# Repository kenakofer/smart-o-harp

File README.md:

## Summary

This site details an ongoing project to improve the chord selection mechanism on chromatic Autoharps/Chromaharps (hereafter called just "autoharps"). An arduino reads inputs from a keypad, computes the desired chord from the keypresses, and mechanically dampens the undesired strings.

It does **not** strum or pluck for the human, nor does it change chords without human input.

See [Motivations](#motivation) for why this project is useful.

See [Dampening Mechanism](#dampening-mechanism) for an for detailed analysis of dampening mechanism possibilities.

See [Avoiding harmonic nodes](#avoiding-harmonic-nodes) on the importance of considering harmonics when experimenting.

See [Keypad → Notes logic](#keypad--notes-logic) for more discussion than you wanted about sensible chord setups.

See [Wiring and Components](#wiring-and-components) to see how and with what it can be constructed.

--------

## Motivation
#### Autoharps are limited in number/variety of chords

Most autoharps have between 12 and 21 chord bars, with the ability to play in only some of the 12 musical keys. The chords available are usually major chords, minor chords, major-minor 7 chords, and sometimes a diminished chord.

Thinking just about these 4 types of chords, the maximal manual autoharp can play 21 of them, out of the `12*4=48` possible.

Stepping out of the chord bar paradigm can allow more flexibility.

#### Ergonomics of chord layouts can only go so far, and are not always key agnostic

The best layout I've found with 21 bars is to have each column be of the form (from farthest reach with the left hard to closest): `(Am, C, A7)`. Successive columns just walk this around the circle of fifths. This makes playing most major and minor songs in 5 key signatures ergonomic and *key agnostic* (transposing a song is as simple as shifting your chording hand over). Still, one of several flaws with this layout: When one wants the major/minor version of the minor/major chord, it's a wide reach that may go off the harp.

Stepping out of the 1 button = 1 chord paradigm can allow more flexibility.

#### Playing autoharps for long periods can cause cramping, arthritis, or other joint pain in the chording hand.

Depending on how well tuned the harp is and how the hand is positioned, this may be more or less of an issue. I don't play for more than an hour at a time, due to cramping.

Stepping out of the finger-force dampening paradigm etc.

----------

## Dampening mechanism

3 possibilities for this:

#### One solenoid per string

This is my current pursuit. Every string has a small solenoid positioned so that the unpowered state is dampening the string. When powered, the dampener lifts up, allowing that string to sound. The arduino controls the 30-40 solenoids individually, allowing more flexibility than the other two solutions. Cheap solenoids will cost around $1. The batteries I've tried cannot deliver the amps needed, so I'm trying a 12V, 5A laptop charger for now.

**Construction summary**: From a autoharp with exposed chord bars. Remove all bars except for one. Stretch the springs holding that bar so that the bar stays high under more force. Super glue solenoids to the sides of the bar such that the solenoids head is just short of touching the string it should dampen. Padding can then be glued to the head of the solenoid so that the resting state dampens the string effectively. Alternate placing solenoids on each side of the bar to give them enough lateral space.

**Considerations**: Size, shape, material of the dampening pads. Force of dampening. Lower notes' pads need more contact with the string to effectively dampen.

**Pros**: String by string flexibility for chord building, simple construction

**Cons**: Raised solenoids (undampened strings) draw current while remaining raised (one of my tiny $1 solenoids needs at least 70 mA to start lifting, and will continue to draw that while raised).

**Edit 01/13/2020**: On the second build iteration, I found solutions to the energy usage issues.

First, using a [voltage regulator](https://www.amazon.com/DROK-Converter-5-3V-32V-Regulator-Transformer/dp/B078Q1624B/), I was able to reduce the voltage to 9.5 or 10 volts, which reduces current through each solenoid. Each solenoid now needs about 140mA to raise.

Second, one of the solenoids only needs a tiny fraction of that power to stay raised, so the arduino can regulate down the power after a short time, greatly reducing energy costs.

This was a big problem to solve: It makes the prospect of raising all solenoids at once manageable, battery solutions are far more feasible, and the solenoids and components don't get super hot anymore!

#### Depress single-note bars with motor push

This is the second simplest solution. There are 12 "chord" bars, but their felts are cut so that one dampens only the `C`s, one dampens only the `C#`s, etc. Now to form an arbitrary chord, press down the set of bars that correspond to the pitch classes you **don't** want in the chord. Each depression will probably require more force than small solenoids can probably supply, so higher torque stepper motors may be better.

**Construction summary**: From an autoharp with exposed chord bars, take 12 bars and cut their felts to only dampen one pitch class. Replace them in a way to avoid damping on harmonic nodes. Get 12 high torque stepper motors with arms that swivel to straight down (to depress a bar). Mount them above the bars somehow, taking into account their difficult dimensions and the point of downward force on the bar relative to the strings being dampened. Given my lack of construction experience, this last task was too daunting for me.

**Considerations**: Force of dampening. Avoiding harmonic nodes.

**Pros**: Minimal power usage when not changing chords. May be cheaper than the solenoids if done effectively.

**Cons**: Complicated mounting that occupies space in front of chord bars, which may get in the way of the strumming hand.

#### Depress single-note bars with down pulling strings

I only mention this because I seriously tried making it work for a bit. Wouldn't recommend it.

Like the above in terms of the single note bars. For each bar: Tie a string to each end, run it straight downward and around a pivot point, then pull on both ends to depress the bar. Use a motor head to pull the strings taut to dampen a note.

**Considerations**: Allowing the motors to do no work when not changing chords. Motors need to have some torque.

**Pros**: The complicated mounting of the previous can be relocated somewhere less invasive (inside the autoharp body would be really interesting.

**Cons**: Starting to get quite complicated.

--------

## Avoiding harmonic nodes

See the [Wikipedia article](https://en.wikipedia.org/wiki/Harmonic) if you don't know what a harmonic node is. To experience it, place your finger or an eraser exactly halfway along a string, and pluck the string. An octave above the string's note will resonate. Slide along the string to find other points where the string will still sound.

That point on the string is a harmonic node, and is a poor location for a felt to dampen sound. There are other harmonic nodes at `(1/3, 2/3, 1/4, 3/4, 1/5, 2/5, ...)` etc. (all the rational numbers between 0 and 1). As the denominator gets bigger, it matters less in this context.

Whenever we mess with positions of bars and felts on the autoharp, we need to keep this consideration a priority to minimize extraneous noise while strumming. Consider marking all the harmonic nodes on the strings (e.g. with a red marker) before deciding on bar/felt placements that avoid those spots.

-------------

## Keypad &rarr; Notes logic

***Edit 01/13/2020***: If you don't care about motivations and thought processes, skip all this (very interesting) stuff past self wrote. I'll cover my current favorite keypad layout in [On Second Construction](#on-second-construction). That said, I still basically agree with all of this, past self just overlooked a few possibilities and didn't have enough buttons to press.

This project has the opportunity for a very consistent, learnable, ergonomic, key agnostic chord control mechanism. Optimizing for all these is a real puzzle, and different musicians will have different opinions and desires in this area.

Thankfully, the code on the arduino is far more easily changed than the mechanics of the construction, so we don't have to build a new autoharp if we forget a chord.

In this section, there will be tension between 1) incorporating more buttons/controls/physical complexity into the design, so that the amount of interaction needed to change to arbitrary chords is minimized, and 2) having fewer buttons/controls, so that the size/cost/physical complexity is minimized, but more interaction is needed to specify arbitrary chords. Each person probably has their own balance, but I lean more toward the fewer buttons/controls because I'm bad at electronics.

#### Music Theory Considerations for important triads

In a major key, here are the roman numeral chords I want easy access to, in decreasing order of importance: `(I, V(7), IV, vi, ii, II(7), iii, III(7), vii°, VI, VIIb, ...)`  I have high uncertainty after halfway through that list.

Similarly, in a minor key (using the roman numeral `vi` as the tonic chord for consistency): `(vi, iii, III(7), ii, V(7), I, IV, ...)` I have high enough uncertainty that I won't try to add more.

Songs with the richest harmonies have both minor and major progressions in them, so it behooves us to not only make the system key agnostic, but also *tonality agnostic* (a term I just made up: a song that starts major and then goes minor or vice versa shouldn't throw us for a loop).

The first 7 elements of each list have 6 in common, which (probably due to some arcane property of (meta-)music-theory) are also six-in-a-row around the circle of fifths: `(IV, I, V, ii, vi, iii)`.

Or, arranging them in rows as autoharpists typically do:

|     |     |     |
| --- | --- | --- |
| IV  | I   | V   |
| ii  | vi  | iii |

This seems like an optimal arrangement of 6 buttons for playing diatonically, to be key and tonality agnostic. I'll treat these 6 chords as the core chords, which should be accessible through a single button press.

To actually make it key agnostic though, there needs to be a way to play in more than one key.

**Fixed chord root buttons**: We could do this with static buttons by having 24 buttons that we could arrange in 2 literal circles of fifths. The circles could be one inside the other, and then we literally have a circle of fifths as a control board:

24 buttons feels like a lot, but it gives us every major/minor triad, and it could make for a really attractive circular keypad, which could rotate to "switch" keys, and have modifier keys inside or outside the main circle. You would have to construct this yourself, as I can't find such a circular keypad online, even just for one row.

If your thumb is used to joysticks, another idea is to map the sectors of a joystick's movement to the circle of fifths. The lack of tactile feedback on the boundaries between chords, or the small 30&deg; sectors might be issues.

**Dynamic chord root buttons**: We can try to use program state to do it with fewer buttons: 6 buttons could code for `(IV, I, V, ii, vi, iii)` as in the table above, and 2 buttons could be used to change our key. Each button can change the key one direction or another around the circle of fifths. This has the disadvantage of not being able to jump to some arbitrary chord root outside the key: `VIIb` and `VIb` come to mind as somewhat common examples. And the chord `vii°` is entirely in the key and we can't reach it either.

The biggest problem is that the II and III chords aren't there. Adding another row can fix that, and also gives us all of the first 7 most important chords in major and minor from above:

|     |     |     |
| --- | --- | --- |
| IV  | I   | V   |
| ii  | vi  | iii |
| II  | VI  | III |

This third row looks a little redundant next to the second row; especially if the "Swapping major/minor triad" modifier below is convenient to use.

#### Music Theory considerations for chord modifiers

We can expand the possibilities of these chords with modifiers. A modifier is a way to add or modify the notes in the 24 basic triads. Ideally, several modifiers could be added to one triad without much hassle. Each player will probably have a different preference for how these are arranged and which are included, or may even desire to change layouts between songs.

Here's my list of modifiers in decreasing order of importance and increasing order of my excitement: Adding a minor seventh, switching major/minor to minor/major triad respectively, diminishing the chord, sus4-ing the chord (!!), adding a major seventh to the chord (!!!), augmenting the chord (!!!!). There could be add2, add6, 9, 11, 13 stuff as well.

**Adding sevenths**: The major point of contention with having a `+7` modifier button is whether that 7 should be major or minor or context dependent. Chords with a major 7th above the root are rare, and seldom used outside of jazz. [Mechanical autoharps aren't great for jazz](http://jazzmando.com/new/archives/001511.shtml) (Only view if you aren't easily offended), and the possibility for major sevenths would help.

It isn't usually possible to predict the presence of major sevenths from the key signature, and chord sheets are explicit about when the 7 is major: `FM7` or `Fmaj7`. For this reason, it seems most best to use two separate modifiers: A `+min7` button that is in very easy reach for frequent use, and a `+maj7` button if the player wants it.

Alternatively, consider that a single button could be double tapped to get a different behavior, e.g. `+7` once for `+min7` and twice for `+maj7`.

**Swapping major/minor triads**: A `ii` becomes a `II`. A `iii` becomes a `III`. A common progression at the end of songs: `(I - iv - I)`. The `IV` and `V` in a major key get swapped out with their parallel minor counterparts for a more edgy harmony. The [Picardy third](https://en.wikipedia.org/wiki/Picardy_third) makes the last chord of a minor song (un)expectedly major.

Though a minor button and a major button separately are simpler to understand, the minor button would only be useful on major chords, and the major button only on minor chords. Combining them into a single button saves a button for something else.

**Diminished chords**: Three chords of interest: a [diminished triad](https://en.wikipedia.org/wiki/Diminished_triad) (3 notes with minor thirds between them), [fully diminished seventh chord] (https://en.wikipedia.org/wiki/Diminished_seventh_chord) (4 notes with minor thirds between them), and [half-diminished seventh chord](https://en.wikipedia.org/wiki/Half-diminished_seventh_chord) (a diminished triad with a minor seventh on top). The logic I've used thus far does not fit diminished chords well: We don't have `vii°` the most common diminished triad in our base triads; if we did, we still don't have a modifier to add a minor sixth to the chord for the fully diminished seventh. The most comprehensible solution is simply to add a modifier for each variation.

There are a few inelegant hacks we can use if we don't want to add so many buttons for these relatively rare chords. We could add one modifier button, a `dim` button, but have the button work in coordination with our `V` triad to produce the `vii°`. Why `V`? The diminished triad has a (dominant function)[https://en.wikipedia.org/wiki/Dominant_(music)] just like the `V`, and a `V7` can be thought of as a `vii°` with an added fifth scale degree.

We can co-opt other buttons that will not be much use in diminished chords, such as the `+maj7`, to be a `+min6` for the fully diminished chord. We can use the `+min7` as is to produce a half-diminished chord. Each of these chords would require 3 button presses: the `V`, the `dim`, and whichever `+7` button.

**Augmented chords**: These are a piece of proverbial cake relative to the diminished chords. An [augmented triad](https://en.wikipedia.org/wiki/Augmented_triad) is 3 notes separated by major thirds. Ignoring enharmonics (as I do) there are only 3 different augmented chords. So throw on an `aug` button, hit it with `I` or `iii` and you'll get the same effect. The `+7` modifiers are still there if you want to play a really exotic chord.

**Sus4 chords**: In a [sus4 chord](https://en.wikipedia.org/wiki/Suspended_chord) the 3rd is removed and a perfect 4th added. Pretty straightforward unless you want to hack together a more general system to get `sus2` without extra buttons, but I'm cool with just a `sus4` for now.

**You get the idea**: Other modifier ideas: removing the third to make open fifths, removing third and fifth to make octaves (yawn). "Scale" modifiers could be used for allowing playing any notes inside the scale by damping the ones outside the scale. Diatonic scale, pentatonic scale, various minor scales, or other less common scales.

#### Misc. operator buttons

**Left/Right around the circle of fifths**: 2 buttons, `mod5` and `mod4` to allow the instrument to change keys in two directions: `V` becomes `I`; and `IV` becomes `I`. Modulating by minor thirds might also be useful to go quickly between parallel major/minor keys.

**Previous chord**: There are frequently times when you are walking a melody up a scale and have to go back and forth between passing chords. Having a `prev` button to go to the chord just before the one currently playing could save 1 or 2 key presses depending on how complicated the chords are.

#### Keypress timing considerations

Timing is very important and has not yet been discussed. Some keypads do not support detecting multiple keys pressed at the same time, so combinations of keys pressed to produce a chord cannot happen at once. We will call this a _sequential_ keypad system. Many more keypads have, at least in their hardware, the ability to correctly detect certain simultaneous keypresses, but not others. We'll call a system that can detect some number of simultaneous keypresses correctly a _simultaneous_ keypad system. We'll start with thinking sequentially for simplicity's sake.

#### Sequential principles

Most of the time when you press the `IV` button, you just want to play that chord as is. But suppose one time in the middle of a song it's a minor `iv` chord, requiring the major/minor modifier plus the `IV` button. Thinking sequentially, one button press has to come before the other.

If the `IV` is first, the arduino can either 1) wait for more input, or 2) immediately make the chord available with possibly the wrong tonality.

If the `maj/min` is first, the arduino can either 3) wait for more input, or 4) immediately change the current chord to the opposite tonality.

Of these 4 scenarios, I like 3 best. Immediate changes mean the instrument will be in states of the wrong tonality. If the arduino is to wait for something, it's best that the "something" be definite. We've talked about the 6 fundamental triad controls, and one reason they are so fundamental is that they are the common element, and thus can safely be the element that actuates the changing of the chords in one quick motion.

Say we're in C major, and we want to play `E7`, which is `III7`. So the order of the sequential presses would be `maj/min`, `+m7`, `iii`. Only pressing the final button would cause the dampened strings to change. Not gonna lie: this sounds painful given how often I use `III7`.

#### Sequential layout ideas

Given the above, here are some of my ideas for "good" sequential keypad layouts. Any of these could have part or all of it rotated 90&deg; to better fit under the fingers.

**12 button sequential keypad A (fast and simple):**

|     |     |     |
| --- | --- | --- |
| IV  | I   | V   |
| ii  | vi  | iii |
| II7 | VI7 | III7|
| mod4|+min7| mod5|

This layout should play melodies quickly and efficiently. The presence of the third triad row (with 7s already added because of their nearly universal use on secondary dominants) allows us to leave out `maj/min` modifier. We can play most chords with a single keypress, with the exception of the `V7` (this is a real downer). Even with just these 12 buttons, the player can play in all 12 key signatures, major and minor, with the most common chords, have minor chords with minor sevenths, major sevenths if you use a double-tap logic, and modulate keys mid song without fuss. 

Some players might like swapping out the `+min7` for a `V7` button, or have the double tap behavior provide the `V7`, or some variation on that.

**12 button sequential keypad B (slower and deeper):**

|     |     |     |
| --- | --- | --- |
| IV  | I   | V   |
| ii  | vi  | iii |
|+min7|maj/min|sus4|
| mod4|prev | mod5|

We remove our convenience row of chords to add more cool modifiers to show off with. Double taps would open open up more possibilities `+min7`  &rarr; `+maj7`; `maj/min` &rarr; `dim`; `sus4`  &rarr; `sus2`. But here the secondary dominants with sevenths require 3 presses. This could be fine for chording and slower melodies, but not faster ones. The `prev` button recovers some speed between alternating chords.

#### Simultaneous principles in row, column keypads

The possibility of pressing multiple keys at the same time allows for faster fingering of chords with modifiers, but introduces complexities of hardware and timing. For a better introduction to these issues on a typical computer keyboard, [see here](https://en.wikipedia.org/wiki/Rollover_(key)).

**No ground pin**: It's common for keypads to be wired such that each row and column corresponds to a pin, such that pressing the button in the first row and first column connects the first row pin (`row1`) to the first column pin (`col1`). Suppose that the button in the first row, second column is also pressed. then `row1`, `col1`, and `col2` are all connected to each other.

But the arduino's logic is in reverse: (Ex. 1) If it sees that `row2`, `col3`, and `col4` are connected to each other, can it know for certain what buttons are pressed? In this case, yes, because a button press is always at the intersection of a row and column, and a row or column pin can't be in the connected list without having a pressed button. We can extend this logic to say that any number of keypresses in any single row or in any single column are always safely distinguishable.

(Ex. 2) If `row1` and `col1` are connected, and `row2` and `col2` are separately connected, the arduino still knows the exact two buttons that are pressed. This, along with the first example, shows that any two simultaneous keypresses are distinguishable.

Certain combinations of 3 simultaneous keypresses introduce ambiguity. (Ex. 3) If ever there is a pressed button (e.g. `row1, col1`) who has another pressed button buddy in their row (`row1, col2`), and also a pressed button buddy in their column (`row2, col1`), then all the arduino sees is a group of 4 connected pins: `row1`, `row2`, `col1`, `col2`. Some combination of 3 or 4 of these were pressed, but there's no way to know which. 

However, ambiguity is not necessarily a deal-breaker: as long as the arduino has a sensible default for how to interpret specific situations of ambiguity, it can use that default. We just want to avoid designing a system that allows two useful "button signatures" to have the same "pin signature" from the arduino's perspective.

**With ground pin**: My keypad is weird in that it has a pin that connects to every button, which I'll call the `ground`. So pressing the top left button connects `row1`, `col1`, and `ground`. So Ex. 2 isn't a possibility, because all button presses connect the entire set of row and column pins involved. So the only unambiguous button presses are, as descibed in Ex. 1, within a single column or within a single row. The same note about ambiguity applies.

I'm honestly not sure where I got this keypad, or why I would want this `ground` pin when it seems to only decrease the functionality.

**Regardless**, it is safe for us to make plans for simultaneous keypresses in a single row or column. This limitation still allows quite a few possibilities, but makes simultaneous modifier keys, like a `+min7` difficult to put somewhere that is usable by all the relevant chords. As a result, I'll try to avoid having modifier keys at all.

**12 button simultaneous keypad (Bear With Me edition):**

This will get kind of complicated to diagram now. It's better to have lots of choices IMHO, but I realize many will disagree with me. Note that "2 buttons to the left" will sometimes mean wrapping back around to the right side.

**Interpretation:** Default chord (chord when button to the left is also pressed) (chord when the 2 buttons to the left are both pressed)

|     |     |     |     |
| --- | --- | --- | --- |
|  VIIb (vii°) (vii°7) | IV (IV7) (IVmaj7) | I (I7) (Imaj7)  | V (V7) (Vmaj7)   |
| v (iv) (i)  | ii (II7) (ii7) | vi (VI7) (vi7) | iii (III7) (iii7) |
| mod4 | prev | +sus4 | mod5 |

First off, I sincerely apologize for the first column, you may ignore it as you are picking up the pattern of the rest of the table. 

Pressing a bunch of buttons in a row are interpreted as a modifier on the rightmost of the buttons pressed (wrapping from left to right is important, e.g. to get the `vii°` one would press `VIIb` and `V`). This mostly serves to add various sevenths to chords, and differs between the major and minor triads.

**Major**: When 1 button to the left is pressed, it does `+min7`. When 2 buttons are pressed, it `+maj7`s the chord.

**Minor**: When 1 button to the left is pressed, it majors it and does `+min7`. When 2 buttons are pressed, it just `+min7`s the chord. I didn't use `+maj7` because that isn't as much used on minor chords.

And the first column just throws in all the things I would be sad not to have, in a vaguely circle-of-fifths-y way. This layout throws easy comprehension out the window in favor of packing in the options in an ergonomic manner (Imagine alternating between fingerings for `I` and `V7`, just by lifting a single finger, or doing the same between `III7` and `vi`).

Note that on a grounded pin keypad, the `+sus4` introduces ambiguity when pressed simultaneously with, say, `V`. It connects pins `row3`, `col3`, `row1`, and `col4`. However, if we are content with only using `+sus4` with a single other button press, and not using the other buttons in the 3rd row with the triad buttons, we can have the arduino interpret this ambiguity predictably as using the `+sus4` with whichever button is diagonal to it. No-ground-pin keypads don't need to worry about this.

I'm not sure how useful the `prev` button will be in this layout, because most back-and-forth passing chords are pretty easy to go between already. I add it here mostly because I don't know what else to put in that space. I can't have another typical modifier due to the paragraph above. I could have a parallel minor modifier that is only used with the `mod4` and `mod5` buttons to change key up or down by a minor 3rd easily. Or I could put another chord there, like the `VIb`.

## On Second Construction

This section is written much later. On the second construction attempt, I solved a lot of major issues.

I started over building because the first build was cludgy and bad in its
unfinished state. Here are the major changes in the second construction, in
the software:

 - Using 16 button keypad (4 column, 4 row pins, no weird ground pin
 this time ;) This allows:
 - Different button reading strategy: Use two dimensional array of
 button states rather than row and column states. This allows a lot more
 keypresses without ambiguity.
 - Keymapping to chords substantially rethought. Now it doesn't use ANY
 simultaneous keypresses, but considers some keys as "modifiers" which
 don't do anything when pressed on their own, and "actuators" (maybe
 find better name?) which when pressed immediately actuate a chord with
 whatever modifiers are down. See the big comment in the code for the
 layout.
 - The above means that we were able to get rid of the `buffer_chord`
 system entirely! :celebrate:
 - Chords can now have up to 5 notes to allow for things like Dominant 9
 chords. No reason it couldn't be more.
 - Major power reduction by using pin 10 on the arduino to change
 current flowing to the solenoids. The solenoids need lots more power to
 pop up than they need to stay up, so every chord change starts at
 `FULL_POWER` then drops power usage considerably to `LOW_POWER` after
 `TICKS_AT_FULL_POWER` ticks.
 - Pasted in the function `setPwmFrequency` to use on pin 10, because
 the default, slower frequencies cause audible hums during `LOW_POWER`

Major changes in the hardware that weren't mentioned in the software:

 - I'm now soldering female header pin connectors rather than the components themselves into the soldering board. If I fry another Arduino Nano or break a keypad it will be a trivial swap-out rather than a solder-mess project-killer.
 - Similarly, on each solenoid, I'm putting a jumper cable head on one of the wires. This way, it can be plugged in rather than soldered in. Same logic as above, and flexibility of rewiring on the fly if the autoharp strings are tuned to different pitches.
 - I'm now using a [voltage regulator](https://www.amazon.com/DROK-Converter-5-3V-32V-Regulator-Transformer/dp/B078Q1624B/), which helps me fiddle with and monitor power better. It might not be necessary in the long run, but for a prototype it is _incredibly_ handy to simply bump the voltage up or down.
 - I'm not trying to incororate LEDs this time around. Simpler design, more in my pay grade.

### Most recent keypad layout (4x4 buttons)

My new keypad's hardware doesn't have ambiguity unless 3 or more button presses are at the corners of a rectangular area. This allows some clever setup of held (not simultaneous press!) modifier keys. Getting rid of simultinaety is huge I think.

**Single press with single modifier**

|     |     |     |     |
| --- | --- | --- | --- |
| VIIb | IV | I | V |
| ii | vi | iii | vii° |
| _Make Do_ | _Sus2_ | _Sus4_ | _Maj/Min_ |
| _mM7_ | _MM7_ | _mm7_ | _Mm7_ |

**Single press with double modifier in vertical stacks**

|     |     |     |     |
| --- | --- | --- | --- |
| VIIb | IV | I | V |
| ii | vi | iii | vii° |
| _Dim_ | _Aug_ | _Dim7_ | _1/2 Dim 7_ |
| _(^^^)_ | _(^^^)_ | _(^^^)_ | _(^^^)_ |

Note that:

 - The arrows _(^^^)_ mean that both modifiers must be pressed for the listed modifier to apply. Still, nothing will actuate until a chord button is pressed.
 - Because these modifiers are vertically stacked, it is impossible for a single chord button to form a rectangular area, so hardware ambiguity is avoided.

**Single press with double modifier in diagonal combinations**

|     |     |     |     |
| --- | --- | --- | --- |
| VIIb | IV | I | V |
| ii | vi | iii | vii° |
| | | _Dom9_ | |
|  |  |  | _(Dom9)_ |

Note that:

 - I'm not sure how well these combos will work ergonomically, so I'm only trying one for now. _Dom9_ means Root, M3, P5, m7, M9(M2).
 - Once again, these diagonal combinations avoid hardware ambiguity when one of the chord buttons is pressed

**Horizontal Double modifier as chord button:**

|     |     |     |     |
| --- | --- | --- | --- |
| VIIb | IV | I | V |
| ii | vi | iii | vii° |
| | | VIb | (<<<) |
|  |  | IIIb | (<<<) |

 - These horizontally aligned modifiers would NOT work unambiguously with all chord buttons (If the `I` were pressed, it would look like `V` was also pressed), so it seems reasonable to actually make the modifiers actuate in combination with each other. This means that these particular chords can't have modifiers applied to them to make, for example, a VIb seventh chord.
 - Not all slots are used, because most other chords we really want to be able to add other modifiers

 I'll update the Wiring and Components section at some point, it's outdated for now

--------

## Outdated Wiring and Components

3 main topics here, which others have covered pretty well already so I don't need to. Click the links to read more.

1. [8-bit shift registers](https://www.arduino.cc/en/tutorial/ShiftOut): Getting the (at least) 12 outputs necessary to control 12 systems of solenoids independently, without using up all the arduino's pins.

2. [Driving solenoids with an arduino](https://core-electronics.com.au/tutorials/solenoid-control-with-arduino.html): Except that we will drive the solenoids and the arduino off the same power source, so maybe this isn't super relevant.

3. [Keypad input method](https://www.instructables.com/id/Arduino-Button-Tutorial/): having the arduino read in button presses. This is basic input/output stuff, and the linked tutorial is excellent for looking at a single case. I've covered the specific convoluted logic of my keypad already.

Here's my breadboard setup all laid out. This is diagram version 2, using the nano and fixing some wire placement issues from the first version. 

**Disclaimer**: I'm not great at electronics as I write this. I fried several components on my way to what I hope is a safe, working design.

#### Diagram notes

For every one solenoid shown in the diagram, there will be upwards of 4 solenoids wired in parallel with it, so that all the `C` solenoids share a transistor, and so do the `C#` solenoids etc.

The 4 "extra" outputs could be used to wire the 4 bottom strings of the autoharp individually, so that you can have, for example, the `G7` chord not include the bottom `F`, but still include all the other `F`s.

Other than using 12V to power the arduino on the Vin pin, keep the 12V as far away from the arduino as possible. I fried one Nano by momentarily bridging a connection from 12V to the Nano's 5V pin.

#### Outdated Components list

 * I used [this SB1660 busboard](https://www.amazon.com/gp/product/B00LLOOA0U) for soldering a semi-permanent prototype.
 * Arduino Nano
 * 12V, 5A power supply
 * 2 x 74HC595 chip
 * 12-16 x 1kΩ resistors
 * ~36 x [12V 120mA spring push pull solenoids](https://www.ebay.com/itm/12V-DC-Suction-Micro-Electromagnet-Spring-Push-Pull-Type-Rod-Solenoid-Magnet-4mm/153089629798) (You need one for each autoharp string.)
 * 12-16 x 2N2222 (NPN, BJT) transistors
 * 12-16 x 1N4001 diodes

----

## Code

[Here's the code](https://github.com/kenanbit/smart-o-harp/blob/master/code/code.ino). It's fairly straightforward.

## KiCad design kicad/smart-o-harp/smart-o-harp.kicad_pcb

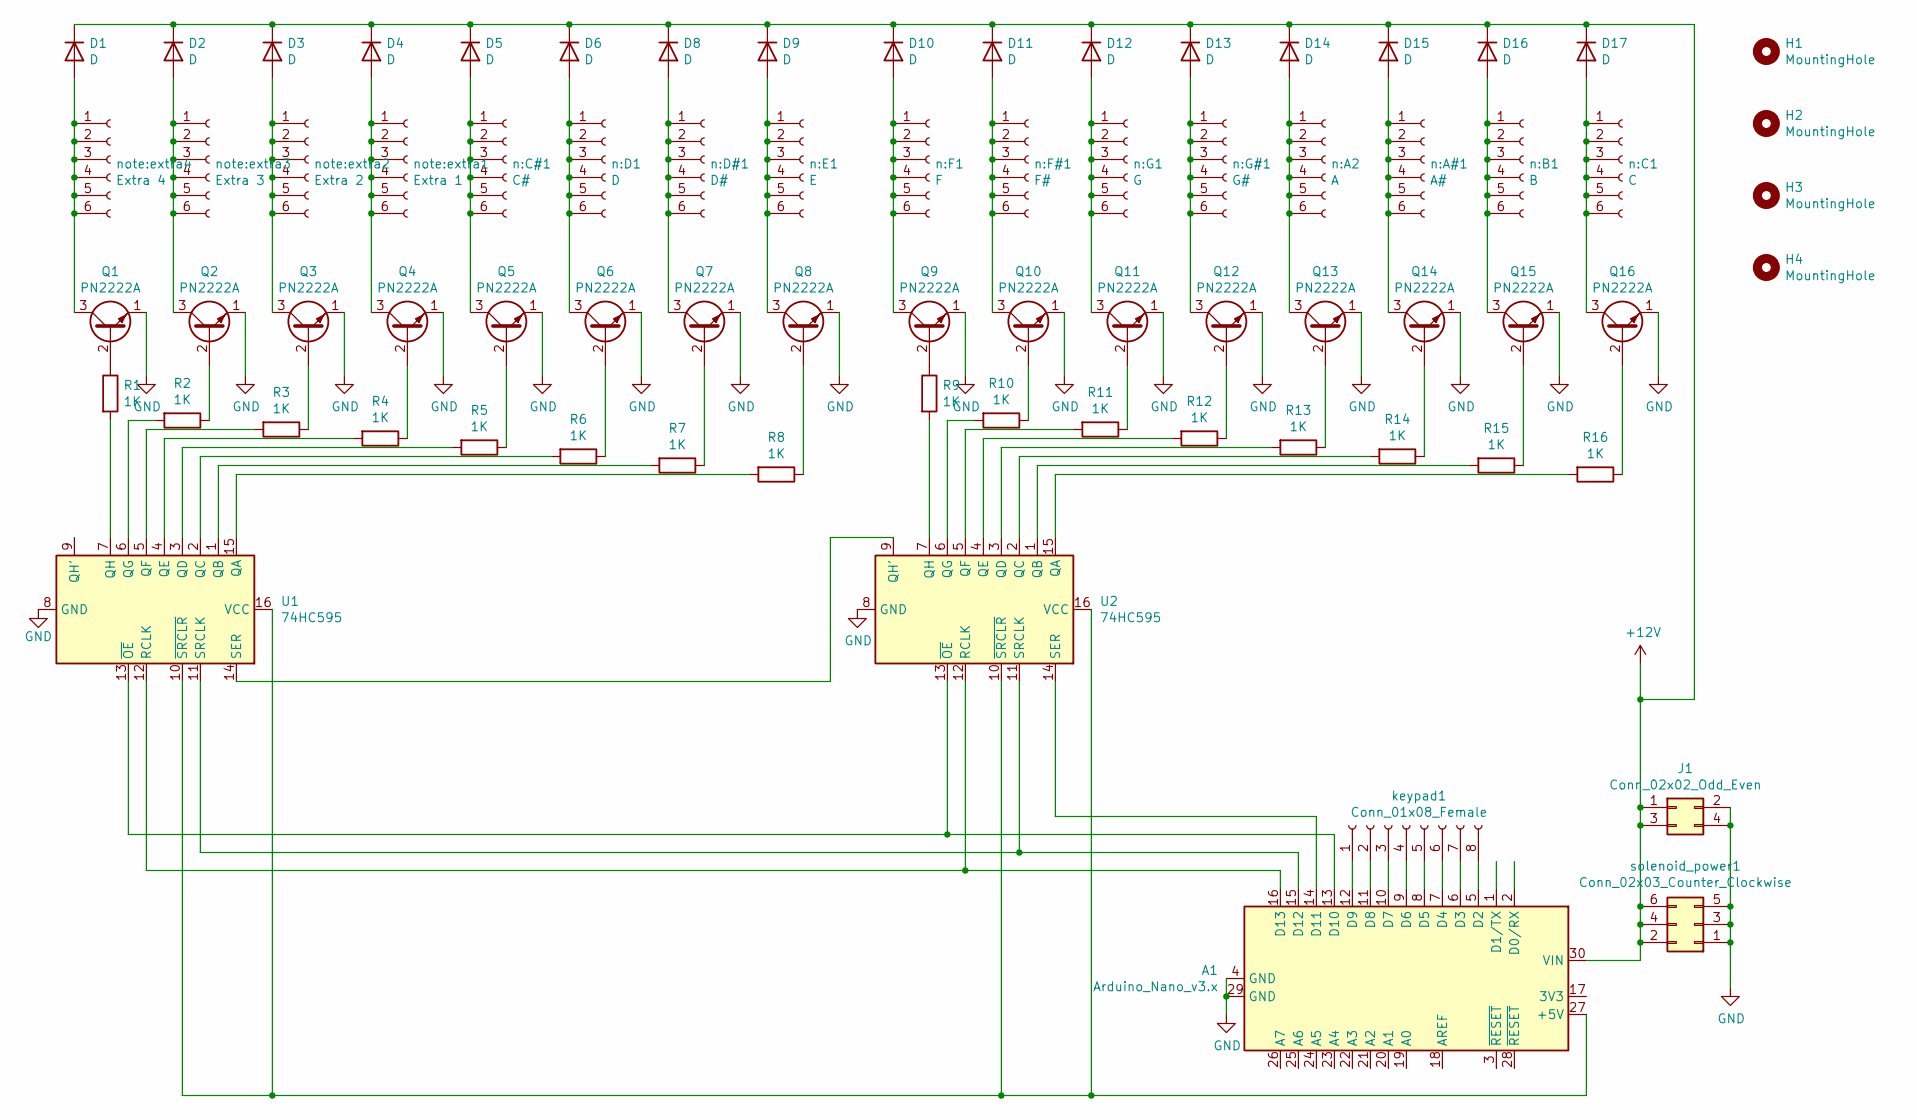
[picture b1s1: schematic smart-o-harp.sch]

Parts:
A1: Arduino_Nano_v3.x; Arduino_Nano
D1, D2, D3, D4, D5, D6, D8, D9, D10, D11, D12, D13, D14, D15, D16, D17: D; D_A-405_P5.08mm_Vertical_AnodeUp
H1, H2, H3, H4: MountingHole; MountingHole_3.2mm_M3
J1: Conn_02x02_Odd_Even; PinHeader_2x02_P2.54mm_Vertical
Q1, Q2, Q3, Q4, Q5, Q6, Q7, Q8, Q9, Q10, Q11, Q12, Q13, Q14, Q15, Q16: PN2222A; TO-92_Wide
R1, R2, R3, R4, R5, R6, R7, R8, R9, R10, R11, R12, R13, R14, R15, R16: 1K; R_Axial_DIN0204_L3.6mm_D1.6mm_P5.08mm_Horizontal
U1, U2: 74HC595; DIP-16_W7.62mm
keypad1: Conn_01x08_Female; PinHeader_1x08_P2.54mm_Vertical
n:A2: A; PinHeader_1x06_P2.54mm_Vertical
n:A#1: A#; PinHeader_1x06_P2.54mm_Vertical
n:B1: B; PinHeader_1x06_P2.54mm_Vertical
n:C1: C; PinHeader_1x06_P2.54mm_Vertical
n:C#1: C#; PinHeader_1x06_P2.54mm_Vertical
n:D1: D; PinHeader_1x06_P2.54mm_Vertical
n:D#1: D#; PinHeader_1x06_P2.54mm_Vertical
n:E1: E; PinHeader_1x06_P2.54mm_Vertical
n:F1: F; PinHeader_1x06_P2.54mm_Vertical
n:F#1: F#; PinHeader_1x06_P2.54mm_Vertical
n:G1: G; PinHeader_1x06_P2.54mm_Vertical
n:G#1: G#; PinHeader_1x06_P2.54mm_Vertical
note:extra1: Extra 1; PinHeader_1x06_P2.54mm_Vertical
note:extra2: Extra 2; PinHeader_1x06_P2.54mm_Vertical
note:extra3: Extra 3; PinHeader_1x06_P2.54mm_Vertical
note:extra4: Extra 4; PinHeader_1x06_P2.54mm_Vertical
solenoid_power1: Conn_02x03_Counter_Clockwise; PinHeader_2x03_P2.54mm_Vertical

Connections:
+12V: A1.30 (VIN), D1.1 (K), D2.1 (K), D3.1 (K), D4.1 (K), D5.1 (K), D6.1 (K), D8.1 (K), D9.1 (K), D10.1 (K), D11.1 (K), D12.1 (K), D13.1 (K), D14.1 (K), D15.1 (K), D16.1 (K), D17.1 (K), J1.1, J1.3, solenoid_power1.2, solenoid_power1.4, solenoid_power1.6
GND: A1.4 (GND), A1.29 (GND), J1.2, J1.4, Q1.1 (E), Q2.1 (E), Q3.1 (E), Q4.1 (E), Q5.1 (E), Q6.1 (E), Q7.1 (E), Q8.1 (E), Q9.1 (E), Q10.1 (E), Q11.1 (E), Q12.1 (E), Q13.1 (E), Q14.1 (E), Q15.1 (E), Q16.1 (E), U1.8 (GND), U2.8 (GND), solenoid_power1.1, solenoid_power1.3, solenoid_power1.5
unnamed: A1.5 (D2), keypad1.8
unnamed: A1.6 (D3), keypad1.7
unnamed: A1.7 (D4), keypad1.6
unnamed: A1.8 (D5), keypad1.5
unnamed: A1.9 (D6), keypad1.4
unnamed: A1.10 (D7), keypad1.3
unnamed: A1.11 (D8), keypad1.2
unnamed: A1.12 (D9), keypad1.1
unnamed: A1.13 (D10), U1.13 (~OE), U2.13 (~OE)
unnamed: A1.14 (D11), U2.14 (SER)
unnamed: A1.15 (D12), U1.11 (SRCLK), U2.11 (SRCLK)
unnamed: A1.16 (D13), U1.12 (RCLK), U2.12 (RCLK)
unnamed: A1.27 (+5V), U1.10 (~SRCLR), U1.16 (VCC), U2.10 (~SRCLR), U2.16 (VCC)
unnamed: D1.2 (A), Q1.3 (C), note:extra4.1, note:extra4.2, note:extra4.3, note:extra4.4, note:extra4.5, note:extra4.6
unnamed: D2.2 (A), Q2.3 (C), note:extra3.1, note:extra3.2, note:extra3.3, note:extra3.4, note:extra3.5, note:extra3.6
unnamed: D3.2 (A), Q3.3 (C), note:extra2.1, note:extra2.2, note:extra2.3, note:extra2.4, note:extra2.5, note:extra2.6
unnamed: D4.2 (A), Q4.3 (C), note:extra1.1, note:extra1.2, note:extra1.3, note:extra1.4, note:extra1.5, note:extra1.6
unnamed: D5.2 (A), Q5.3 (C), n:C#1.1, n:C#1.2, n:C#1.3, n:C#1.4, n:C#1.5, n:C#1.6
unnamed: D6.2 (A), Q6.3 (C), n:D1.1, n:D1.2, n:D1.3, n:D1.4, n:D1.5, n:D1.6
unnamed: D8.2 (A), Q7.3 (C), n:D#1.1, n:D#1.2, n:D#1.3, n:D#1.4, n:D#1.5, n:D#1.6
unnamed: D9.2 (A), Q8.3 (C), n:E1.1, n:E1.2, n:E1.3, n:E1.4, n:E1.5, n:E1.6
unnamed: D10.2 (A), Q9.3 (C), n:F1.1, n:F1.2, n:F1.3, n:F1.4, n:F1.5, n:F1.6
unnamed: D11.2 (A), Q10.3 (C), n:F#1.1, n:F#1.2, n:F#1.3, n:F#1.4, n:F#1.5, n:F#1.6
unnamed: D12.2 (A), Q11.3 (C), n:G1.1, n:G1.2, n:G1.3, n:G1.4, n:G1.5, n:G1.6
unnamed: D13.2 (A), Q12.3 (C), n:G#1.1, n:G#1.2, n:G#1.3, n:G#1.4, n:G#1.5, n:G#1.6
unnamed: D14.2 (A), Q13.3 (C), n:A2.1, n:A2.2, n:A2.3, n:A2.4, n:A2.5, n:A2.6
unnamed: D15.2 (A), Q14.3 (C), n:A#1.1, n:A#1.2, n:A#1.3, n:A#1.4, n:A#1.5, n:A#1.6
unnamed: D16.2 (A), Q15.3 (C), n:B1.1, n:B1.2, n:B1.3, n:B1.4, n:B1.5, n:B1.6
unnamed: D17.2 (A), Q16.3 (C), n:C1.1, n:C1.2, n:C1.3, n:C1.4, n:C1.5, n:C1.6
unnamed: Q1.2 (B), R1.1
unnamed: Q2.2 (B), R2.1
unnamed: Q3.2 (B), R3.1
unnamed: Q4.2 (B), R4.1
unnamed: Q5.2 (B), R5.1
unnamed: Q6.2 (B), R6.1
unnamed: Q7.2 (B), R7.1
unnamed: Q8.2 (B), R8.1
unnamed: Q9.2 (B), R9.1
unnamed: Q10.2 (B), R10.1
unnamed: Q11.2 (B), R11.1
unnamed: Q12.2 (B), R12.1
unnamed: Q13.2 (B), R13.1
unnamed: Q14.2 (B), R14.1
unnamed: Q15.2 (B), R15.1
unnamed: Q16.2 (B), R16.1
unnamed: R1.2, U1.7 (QH)
unnamed: R2.2, U1.6 (QG)
unnamed: R3.2, U1.5 (QF)
unnamed: R4.2, U1.4 (QE)
unnamed: R5.2, U1.3 (QD)
unnamed: R6.2, U1.2 (QC)
unnamed: R7.2, U1.1 (QB)
unnamed: R8.2, U1.15 (QA)
unnamed: R9.2, U2.7 (QH)
unnamed: R10.2, U2.6 (QG)
unnamed: R11.2, U2.5 (QF)
unnamed: R12.2, U2.4 (QE)
unnamed: R13.2, U2.3 (QD)
unnamed: R14.2, U2.2 (QC)
unnamed: R15.2, U2.1 (QB)
unnamed: R16.2, U2.15 (QA)
unnamed: U1.14 (SER), U2.9 (QH')

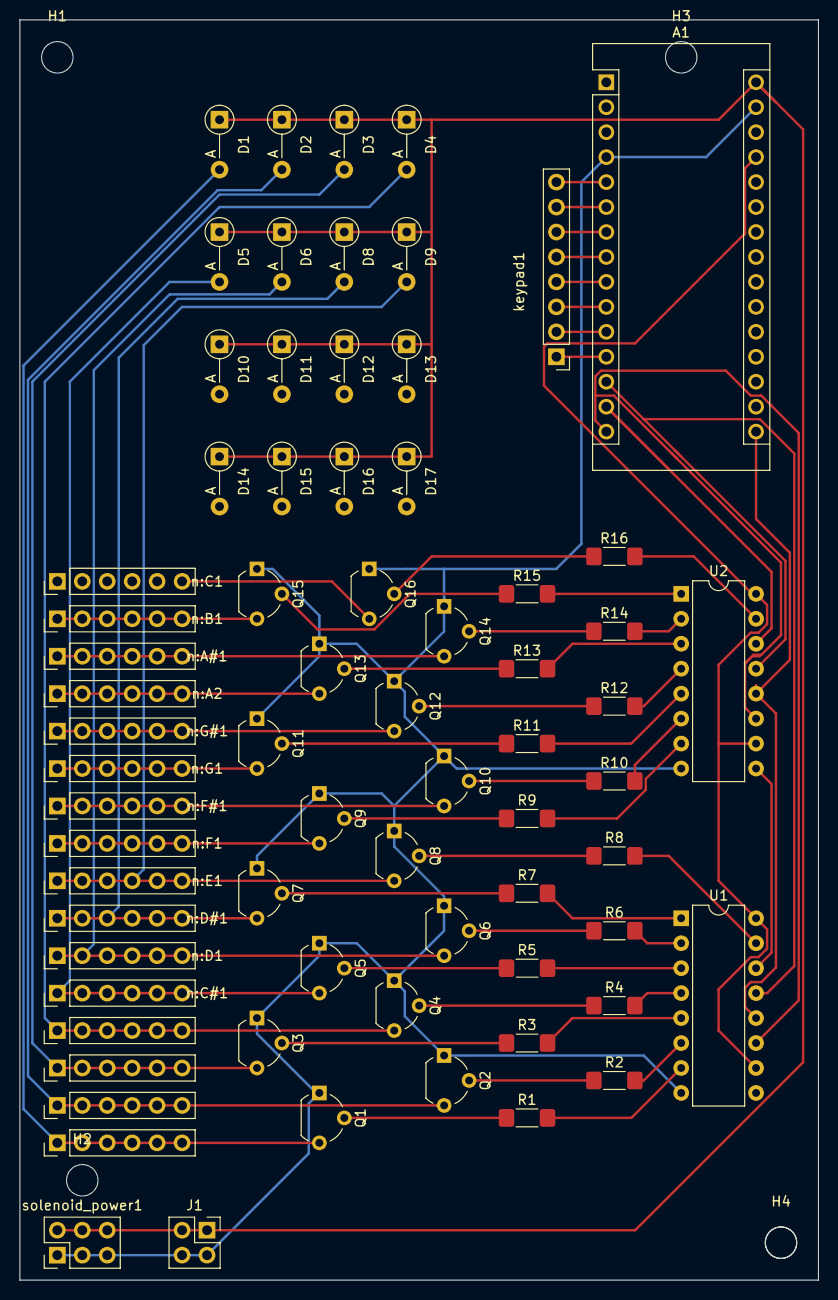
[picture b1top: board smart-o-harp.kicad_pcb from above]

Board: 2 copper layers, 81.3 x 128.3 mm, 74 parts (0 on the bottom side), 64 nets.

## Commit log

2019-03-29 Set theme jekyll-theme-time-machine
2019-03-29 Create basic description of project
2019-03-29 Remove unnecessary title in README
2019-03-29 Add <hr>s, h2s
2019-03-29 Add dampening mechanism section
2019-03-29 bold not
2019-03-29 Add avoiding harmonic nodes
2019-03-29 Add beginnings of keypad to notes logic
2019-04-01 Copy default.html from theme
2019-04-01 Remove current-section header
2019-04-01 Create style.scss for better mobile width
2019-04-01 diminished, augmented, sus4
2019-04-01 Fix lots of css
2019-04-01 Add keypress timings
2019-04-02 Add nice coloring to code blocks
2019-04-02 fix degree signs
2019-04-02 Add 12 button layouts
2019-04-02 Fix typos
2019-04-02 Add icons
2019-04-02 Add links to favicon
2019-04-03 Add simultaneous principles/example
2019-04-03 Remove padding on table cells, min-height/width
2019-04-03 Change font/size of <td>
2019-04-03 Add totally untested code to test keypad
2019-04-04 Get code to compile
2019-04-04 Get input working
2019-04-04 Get basic chord logic framework
2019-04-04 Change <hr> style
2019-04-04 Fill in all the button/chord logic
2019-04-05 Get note output for all chords correct
2019-04-05 Add buffer time to chord change
2019-04-05 Fix indentation
    Using vim 4 space = 1 tab
2019-04-07 Add actuating code
2019-04-08 Reorganize, clean up, document code
2019-04-09 Adding Fritzing breadboard diagram file and jpg
2019-04-19 Update diagram, add components
2020-01-14 Massive changes for 2nd construction
    I started over building because the first build was cludgy and bad in
    its unfinished state. Here are the major changes in the second
    construction, in hardware and software:
    - Using 16 button keypad (4 column, 4 row pins, no weird ground pin
    this time ;) This causes:
    - Different button reading strategy: Use two dimensional array of
2020-01-14 Update README with second construction info
2020-01-17 Write up new 4x4 keypad layout in README
2020-01-22 Make solenoid pin order more explicit
2020-01-23 Step up and down from full and low power
2020-01-23 General addition of variables to code and comment additions
2020-01-24 Solve all unpredictability issues ;)
    It seems to be very important that we are set to full power (0 PWM
    cycle) during the chord change. Otherwise, sometimes when we call
    actuate_current_chord(), the 8 bit shift registers will get the wrong
    data somehow. This was the original software setup, which I thought
    wasn't working originally.
    FULL_POWER doesn't have to be on for all that long, only between 25-50
2020-01-26 Rotate layout of keypad
    It seems more ergonomic to actually orient the left hand downwards
    rather than across the instrument. Thus the rotation of the coordinates.
2020-01-26 Replace sus2 with dom9
    Get rid of sus2 from the keypad entirely. The motivation is that IVsus2
    = Isus4, Isus2 = Vsus4, etc. around the circle of 5ths. Furthermore,
    after playing around with it there doesn't seem to be a huge auditory
    difference.
    The choice to move dom9 to the new spot is that I want to try it out
    more and it was the only modifier using a double diagonal modifier
2020-01-26 Add a NONE chord combo. Feeble attempt at ALL
    The NONE chord is now playable, which just dampens all strings, which is
    the same state the instrument starts in. Pretty basic stuff.
    The ALL chord is more tricky. Raising every solenoid at once is a huge
    power draw, and only sometimes works, pulling the voltage unacceptably
    low and sometimes resetting the arduino. Perhaps I should try a simpler
    solution; this added function may be too complex. In any case, I
2020-01-30 Change out Dom9 for add2
    add2 is very similar to Dom9, but it just lacks the m7 and can be used
    on either a minor or major chord. It has turned out to be surprisingly
    useful in some more edgy suspensions :)
2020-02-01 Untested: Make double actuators more "circle-of-fifths-ish"
    We currently had the VIb and IIIb as near-the-key triads, playable using
    a double modifier combo. Having encountered a need for the IV# (major
    sharp IV) I realized that by adding just that and I#, we could have
    playable chords built on all 12 semitones, if not flexibility of
    tonality for 4 of them.
    The right-side double modifiers represent going out the key in the
2020-02-01 Change major/minor calculations so dim vii modification more useful
2020-02-01 Untested: Change out prev for last_tick
    This find and replace will help be less ambiguous for if I decide to add
    in a "Previous chord" action that will go back to the chord before the
    currently actuated chord.
2020-02-01 Make the keypad layout diagram much nicer and correcter
2020-02-01 Untested: Add PREV functionality
    A press of the PREV button combination will cause the instrument to "go
    back a chord", in other words, change chords to the most recent chord
    played that is different from the current_chord.
2020-02-08 Add auto_play and generalize onpress combo delays
2020-04-09 Add easy seventh adjacent key combos
    Because some of the fastest plucking passages require quickly going `I -
    V7 - I` or `vi - III7 - vi` or similar things, this commit adds the
    ability to press adjacent fifth keys and get the major-minor 7th of the
    right one. For example, pressing I and V yields V7, and pressing iii and
    iv yields III7.
2020-10-01 Revise for 7V power, and add constants for keypad flips
2021-06-03 Commit to push from laptop
2022-06-17 Pull kicad files into repo
